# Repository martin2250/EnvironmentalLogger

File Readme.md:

##Environmental Data Logger

The design files and the software for a small low-power temperature and humidity logger  
Probably the most remarkable feature is the power consumption of just 3.2µA or less
  
a better documentation can be found on [Hackaday.io](https://hackaday.io/project/6177-low-power-environmental-data-logger)  
  
Credits:  
-HD44780 Library by [SA Development](http://www.avrfreaks.net/projects/hd44780-library)  
-I²C Library by [Peter Fleury](http://jump.to/fleury)

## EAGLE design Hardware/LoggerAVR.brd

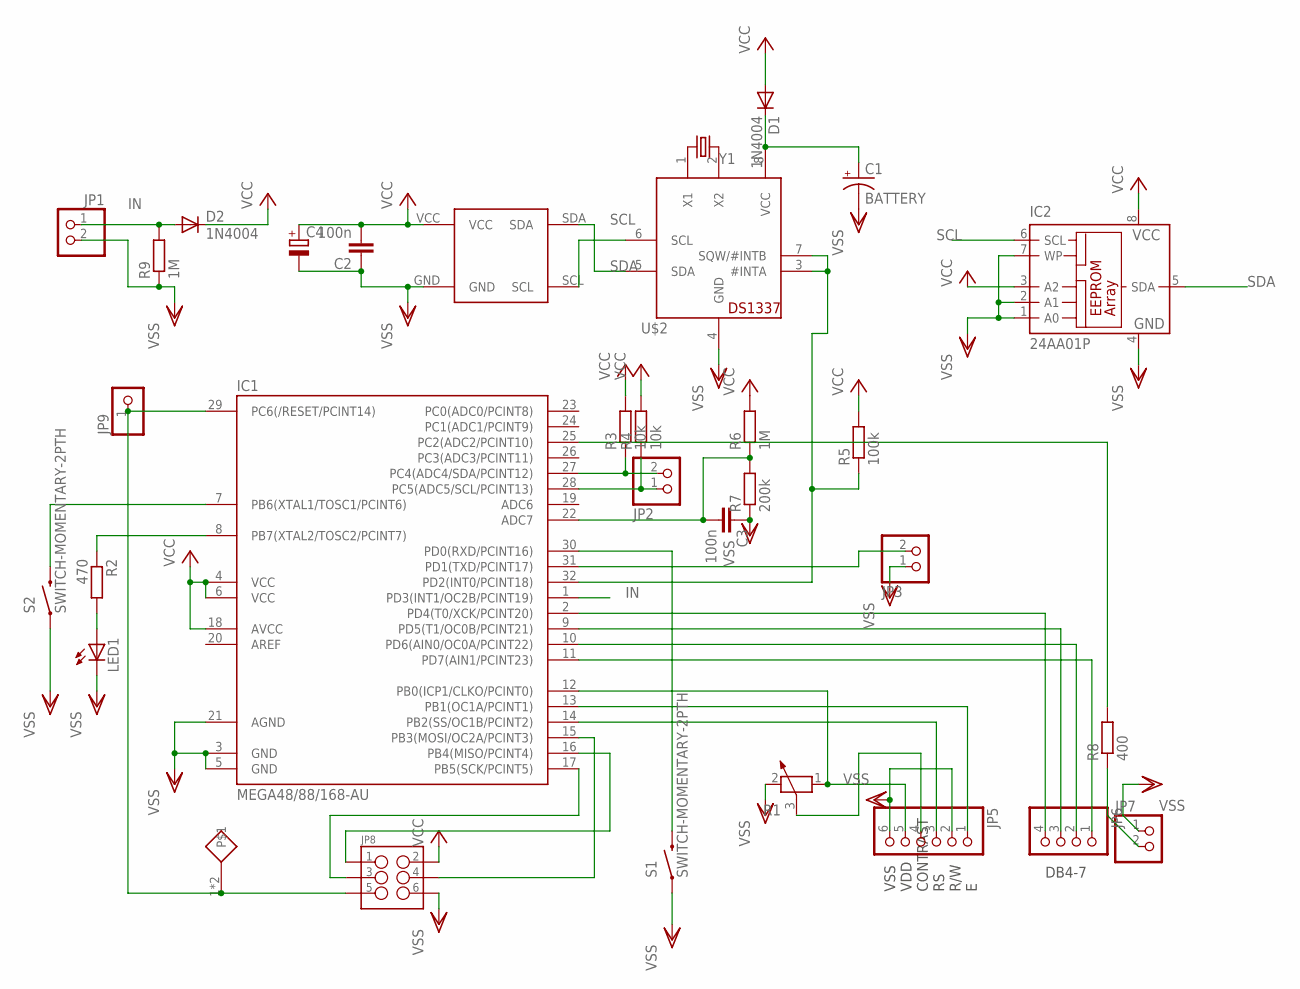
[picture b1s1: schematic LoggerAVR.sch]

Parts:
C1: BATTERY; ETR2
C2, C3: 100n; C1206
C4: CPOL-EUE22-9AXIAL; E22-9
D1, D2: 1N4004; DO41-10
IC1: MEGA48/88/168-AU; TQFP32-08
IC2: 24AA01P; DIL8
JP1, JP2, JP3, JP7: PINHD-1X2; 1X02
JP5: PINHD-1X6; 1X06
JP6: PINHD-1X4; 1X04
JP8: M03X2SHROUD; 2X3-SHROUDED
JP9: PINHD-1X1; 1X01
LED1: LEDSML1206; SML1206
R1: POTENTIOMETER_PT-10; PT-10
R2: 470; M1206
R3, R4: 10k; M1206
R5: 100k; M1206
R6, R9: 1M; M1206
R7: 200k; M1206
R8: 400; M1206
S1, S2: SWITCH-MOMENTARY-2PTH; TACTILE-PTH
U$1: HYT939; TO39
U$2: DS1337; DIL08-ROUND
U$3: 0 - Jump; R1206
Y1: CRYSTAL32-SMD; CRYSTAL-32KHZ-SMD

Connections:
IN: D2.A, IC1.1 (PD3(INT1/OC2B/PCINT19)), JP1.1, R9.2
unnamed: IC1.2 (PD4(T0/XCK/PCINT20)), JP6.4
unnamed: IC1.30 (PD0(RXD/PCINT16)), S1.3 (2), S1.4 (2)
unnamed: IC1.9 (PD5(T1/OC0B/PCINT21)), JP6.3
unnamed: IC1.15 (PB3(MOSI/OC2A/PCINT3)), JP8.4
unnamed: IC1.16 (PB4(MISO/PCINT4)), JP8.1
unnamed: IC1.17 (PB5(SCK/PCINT5)), JP8.3
unnamed: IC1.29 (PC6(/RESET/PCINT14)), JP8.5, JP9.1, U$3.1, U$3.2
unnamed: IC1.10 (PD6(AIN0/OC0A/PCINT22)), JP6.2
unnamed: U$2.2 (X2), Y1.X2 (2)
unnamed: JP5.4, R1.3
unnamed: IC1.11 (PD7(AIN1/PCINT23)), JP6.1
unnamed: IC1.13 (PB1(OC1A/PCINT1)), JP5.1
unnamed: IC1.14 (PB2(SS/OC1B/PCINT2)), JP5.3
unnamed: IC1.31 (PD1(TXD/PCINT17)), JP3.2
unnamed: IC1.7 (PB6(XTAL1/TOSC1/PCINT6)), S2.3 (2), S2.4 (2)
unnamed: IC1.12 (PB0(ICP1/CLKO/PCINT0)), JP5.5, R1.1
unnamed: U$2.1 (X1), Y1.X1 (1)
unnamed: IC1.32 (PD2(INT0/PCINT18)), R5.1, U$2.3 (#INTA), U$2.7 (SQW/#INTB)
unnamed: IC1.8 (PB7(XTAL2/TOSC2/PCINT7)), R2.1
unnamed: LED1.A, R2.2
unnamed: C3.2, IC1.22 (ADC7), R6.1, R7.2
unnamed: C1.+, D1.C, U$2.8 (VCC)
unnamed: IC1.25 (PC2(ADC2/PCINT10)), R8.2
unnamed: JP7.2, R8.1
SCL: IC1.28 (PC5(ADC5/SCL/PCINT13)), IC2.6 (SCL), JP2.1, R4.1, U$1.SCL, U$2.6 (SCL)
SDA: IC1.27 (PC4(ADC4/SDA/PCINT12)), IC2.5 (SDA), JP2.2, R3.1, U$1.SDA, U$2.5 (SDA)
VCC: C2.2, C4.+, D1.A, D2.C, IC1.4 (VCC), IC1.6 (VCC), IC1.18 (AVCC), IC2.3 (A2), IC2.8 (VCC), JP8.2, R3.2, R4.2, R5.2, R6.2, U$1.VCC
VSS: C1.-, C2.1, C3.1, C4.-, IC1.3 (GND), IC1.5 (GND), IC1.21 (AGND), IC2.1 (A0), IC2.2 (A1), IC2.4 (GND), IC2.7 (WP), JP1.2, JP3.1, JP5.2, JP5.6, JP7.1, JP8.6, LED1.C, R1.2, R7.1, R9.1, S1.1, S1.2 (1), S2.1, S2.2 (1), U$1.GND, U$2.4 (GND)

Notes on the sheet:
DB4-7
VSS VDD CONTRAST RS R/W E

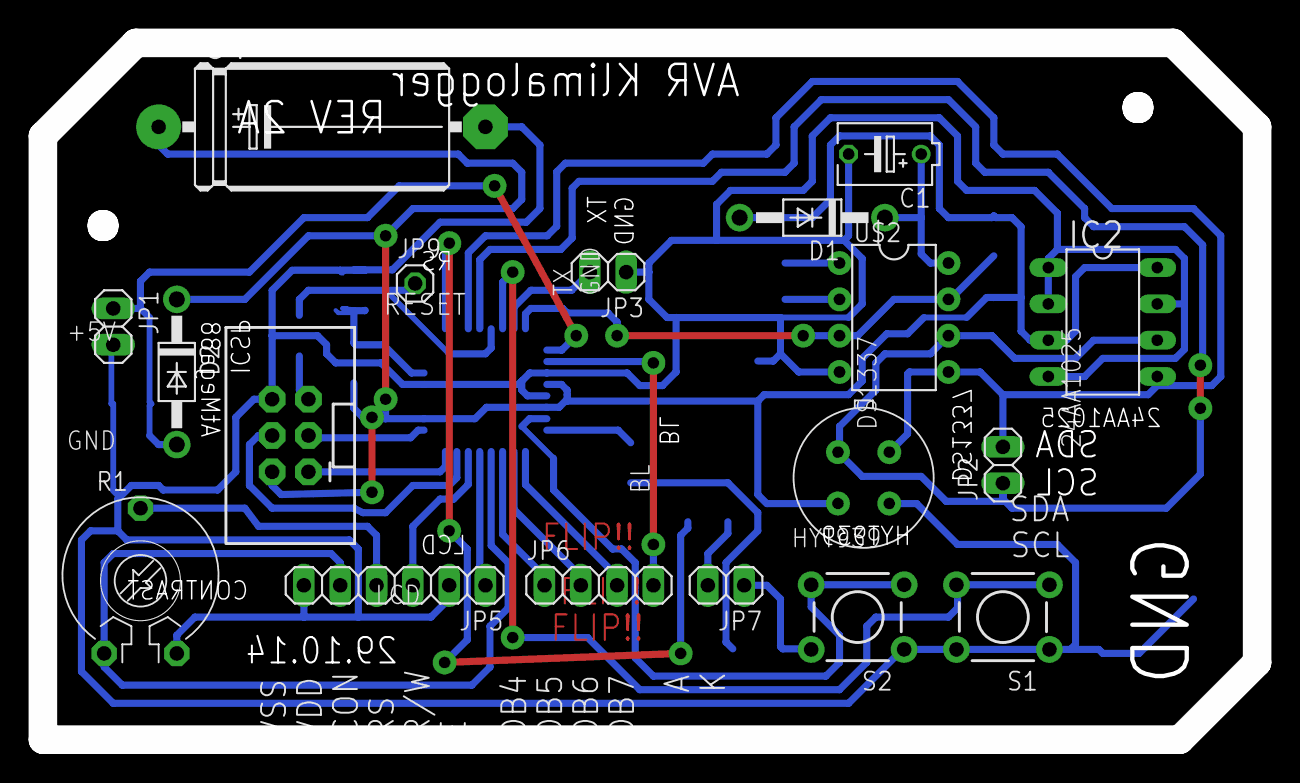
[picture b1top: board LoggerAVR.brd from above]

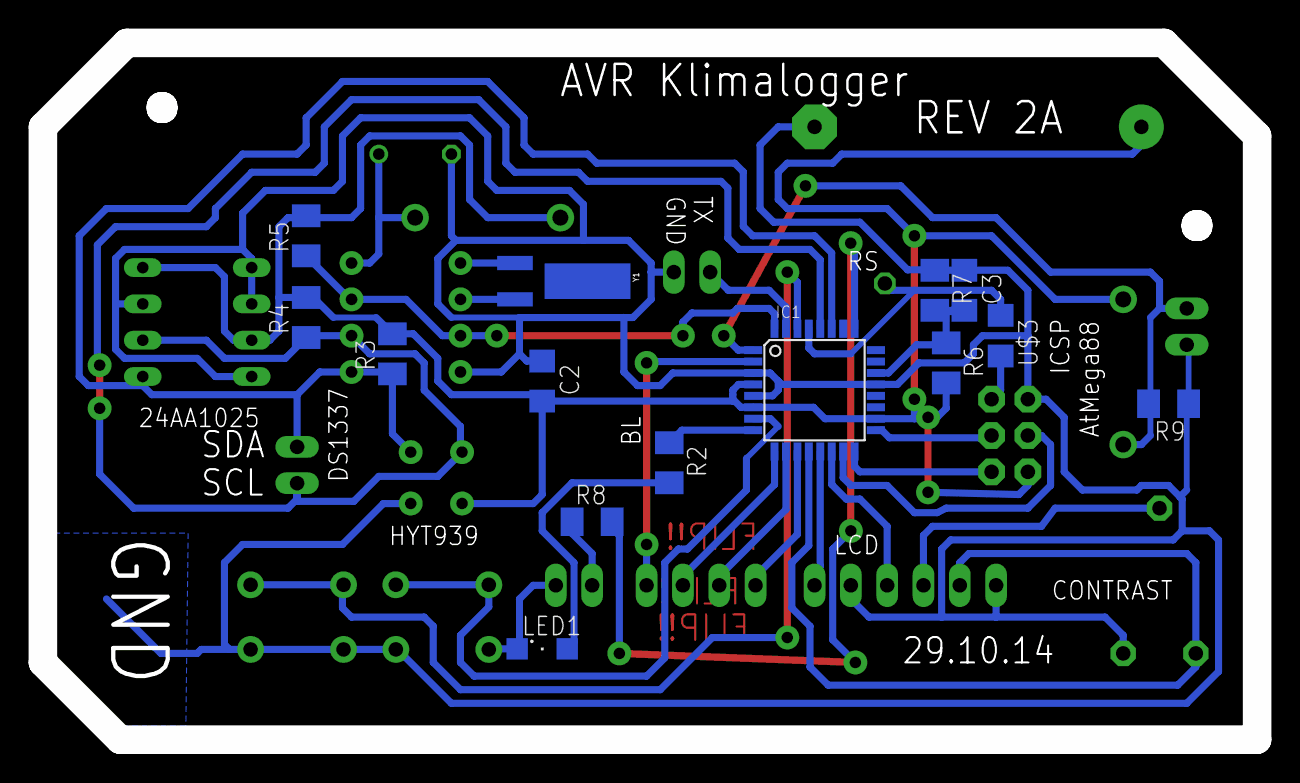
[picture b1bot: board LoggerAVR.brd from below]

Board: 2 copper layers, 84.9 x 48.7 mm, 32 parts (14 on the bottom side), 29 nets.

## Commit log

2015-06-08 :circus_tent: Added .gitattributes & .gitignore files
2015-06-08 Moved Software to /Software/
2015-06-08 Added PC Software, design files
2015-06-27 Removed residue
2018-09-19 Update receive.py
    really need to add arguments to set temp and hum
2018-12-25 fix receive.py

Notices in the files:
parts and their libraries:
SparkFun-Electromechanical: Licensing: Creative Commons ShareAlike 4.0 International - https://creativecommons.org/licenses/by-sa/4.0
